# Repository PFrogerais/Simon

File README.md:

# Démonstration du Jeu Simon – Assemblé & Programmé
Dans cette vidéo, découvrez le jeu **Simon** entièrement assemblé et programmé !  

Ce projet, basé sur une carte Arduino, intègre :
- **4 LEDs** et **4 boutons** pour reproduire la séquence du jeu,
- Un **buzzer** pour les signaux sonores,
- Un **boîtier imprimé en 3D** réalisé sur mesure,

# Dossier de conception du shield Arduino

Voici un guide étape par étape pour concevoir et assembler la carte électronique intégrant des composants CMS (résistances et LED montées en surface) ainsi que des composants traversants (comme le connecteur Arduino et le buzzer). Ce procédé  inclut l'application manuelle de pâte à braser et le passage en four à refusion sans utilisation de stencil.

## 1. Génération des Fichiers de Fabrication

- **Fichiers Gerber :**
- Télécharger [fichiers de fabrication gerber Simon3.zip](hardware/kicad/simon3/production/simon3.zip)
- **Fabrication du PCB :**
- Envoyez ces fichiers à un fabricant de PCB (JLCPCB)

## 2. Nomenclature

| Reference         | Value        |  Qty |
|-------------------|--------------|----- |
| BZ1               | Buzzer       |  1   |
| D1                | LED RED      |  1   |
| D2                | LED Green    |  1   |
| D3                | LED Blue     |  1   |
| D4                | LED Yellow   |  1   |
| J1                | Power        |  1   |
| J2,J4             | Digital/PWM  |  2   |
| J3                | Analog       |  1   |
| R1,R2             | 160          |  2   |
| R3                | 100          |  1   |
| R4                | 150          |  1   |
| R5,R6,R7,R8       | 10k          |  4   |
| SW1,SW2,SW3,SW4   | SW_Push      |  4   |

[Nomenclature](hardware/kicad/simon3/simon3.csv)

## 4. Préparation à l’Assemblage

- **Nettoyage du PCB :**
  - Assurez-vous que la carte est propre et exempte de poussière ou d’empreintes.
- **Mise en place du poste de travail :**
  - Organisez votre matériel : pâte à braser (en seringue), fer à souder pour les composants traversants, four à refusion.
- **Documentation :**
  - Imprimez le schéma et/ou un plan de positionnement (layout) pour guider le placement des composants.

# Brasage des composants

## 1. Application de la Pâte à Braser (Sans Stencil)

- **Utilisation d’une seringue :**
  - À l’aide d’une seringue, déposez manuellement la pâte à braser sur chaque zone de montage des composants CMS.
  - Veillez à appliquer la quantité appropriée pour chaque pad afin d’éviter les ponts de soudure ou les soudures insuffisantes.
- **Précision :**
  - Pour les zones très fines, utilisez une seringue à embout fin et, si besoin, une loupe pour vérifier l’exactitude de l’application.

## 6. Placement des Composants CMS

- **Positionnement :**
  - Placez délicatement les composants CMS (résistances, LED, etc.) sur les pads recouverts de pâte.
  - Vérifiez l’alignement et l’orientation (notamment pour les composants polarisés comme certaines LED).
- **Ajustement :**
  - Corrigez la position des composants si nécessaire avant le passage en four.

## 7. Passage en Four à Refusion

- **Programmation de la courbe de chauffe :**

  - Programmez le four à refusion selon une courbe de température adaptée (phase de préchauffage, pic de température, et refroidissement contrôlé).

- **Refusion :**
  - Placez la carte dans le four et lancez le cycle.
  - Surveillez le processus pour vous assurer que la pâte à braser fond correctement et forme des joints solides.
- **Refroidissement :**
  - Laissez la carte refroidir progressivement pour éviter les contraintes thermiques.

## 8. Soudure des Composants Traversants

- **Placement manuel :**
  - Après la refusion des composants CMS, positionnez les composants traversants (connecteur Arduino, buzzer, etc.) sur la carte.
- **Soudure :**
  - Utilisez un fer à souder pour souder manuellement ces composants.
  - Assurez-vous de réaliser des soudures nettes et sans ponts.
- Utilisation d'une carte Arduino HS pour pour maintenir le shield et les connecteurs 

- Placer la carte par dessus 

## 9. Inspection et Tests

- **Contrôle visuel :**

  - Inspectez la carte à l’aide d’une loupe ou d’un microscope pour vérifier la qualité des soudures (absence de ponts, bonne homogénéité des joints).
- **Retouches éventuelles :**
  - Réalisez des retouches manuelles si vous constatez des défauts.
- **Tests fonctionnels :**
  - Alimentez la carte et vérifiez le bon fonctionnement de l’ensemble du circuit (LED, buzzer, connecteur Arduino).
  - Mesurez les tensions et vérifiez la continuité des pistes si nécessaire.

# Conception du boitier en 3D

Cette section décrit les étapes d'assemblage de votre projet dans un boîtier imprimé en 3D. Le but est de fournir toutes les informations nécessaires pour intégrer les composants électroniques (Arduino UNO, shield, etc.) dans le boîtier final. Le modèle 3D du boîtier, au format STL, est mis à disposition pour que vous puissiez le préparer dans votre logiciel de découpe (slicer) et lancer l'impression 3D.

## Détail des étapes

1. **Modèle 3D du boîtier**

   - **Description :**  
     Vous disposez du fichier STL du boîtier, nommé ici "Boitier Simon". Ce fichier est utilisé avec un slicer pour préparer l'impression 3D de la pièce.
   - **Lien :**  
     [Boitier Simon](hardware/Boitier/simon_box_2-MainBox.stl)  
     En cliquant sur ce lien, vous accédez directement au fichier STL hébergé dans le répertoire `hardware/Boitier/` de votre dépôt GitHub.

2. **Ajouter les inserts à chaud à l'aide d'un fer à souder**

   - **Description :**  

     Avant de monter les composants, il est recommandé d'ajouter des inserts (des éléments métalliques ou en plastique spécialement conçus pour recevoir des vis) dans le boîtier.  
     Pour cela, on utilise un fer à souder qui, en chauffant les inserts, permet de les fixer solidement dans la matière imprimée.
   - **Illustration :**  

     Cette image montre le boîtier dans lequel les inserts ont été placés, prêts à recevoir les fixations.

3. **Ajouter la carte Arduino UNO**
   - **Description :**  

     Une fois les inserts en place, la carte Arduino UNO est insérée dans le boîtier.  
     Cette étape assure que l'électronique de base du projet est correctement positionnée et prête à être connectée aux autres composants.

    - **Illustration :**  

     L'image illustre la carte Arduino UNO insérée dans le boîtier, avec les inserts déjà en place.

4. **Ajouter le shield**

   - **Description :**  

     Le shield, qui est une extension pour l'Arduino, est ensuite ajouté sur la carte.  
     Cette étape complète l'intégration de l'électronique, permettant d'ajouter des fonctionnalités supplémentaires (par exemple, gestion d'entrées/sorties, alimentation, etc.).
   - **Illustration :**  
     
     L'image montre le boîtier avec la carte Arduino UNO et le shield monté, indiquant l'évolution de l'assemblage.

5. **Visser les 4 vis dans les inserts**

   - **Description :**  
     Pour finaliser l'assemblage, 4 vis sont insérées dans les inserts prévus à cet effet.  
     Ces vis servent à fixer solidement l'ensemble des composants dans le boîtier, garantissant une bonne stabilité mécanique.
   - **Illustration :**  
       
     Cette dernière image montre l'assemblage complet, où l'ensemble des composants (boîtier, inserts, Arduino, shield) est maintenu par les vis.

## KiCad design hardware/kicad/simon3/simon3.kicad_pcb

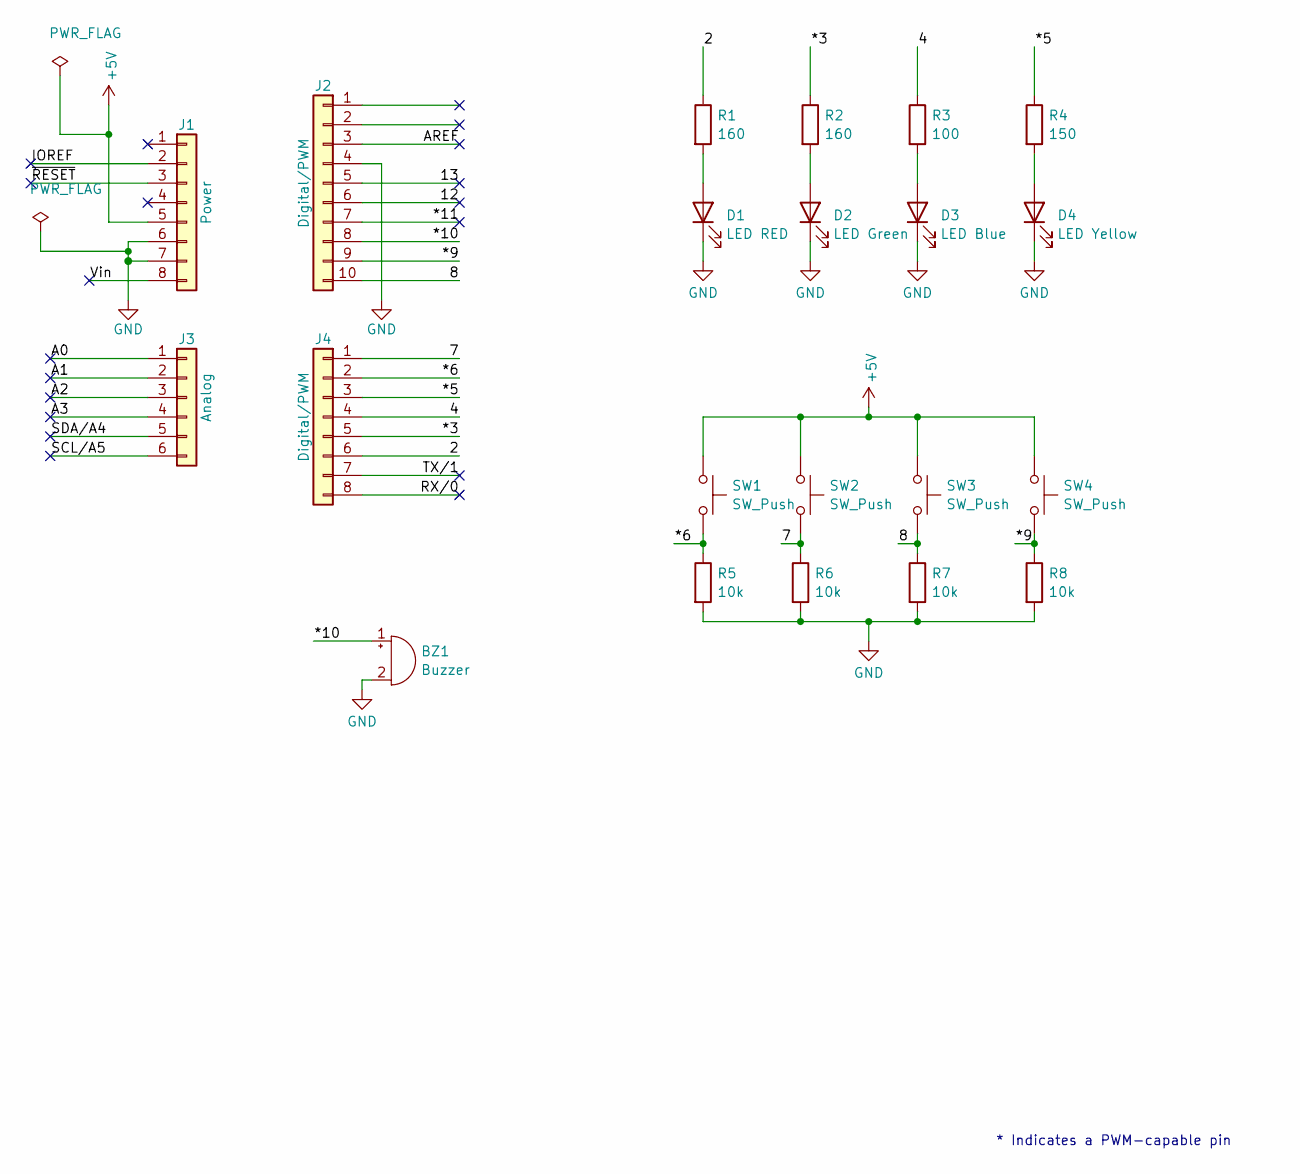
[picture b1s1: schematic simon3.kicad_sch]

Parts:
BZ1: Buzzer; Buzzer_12x9.5RM7.6
D1: LED RED; LED_1206_3216Metric_Pad1.42x1.75mm_HandSolder
D2: LED Green; LED_1206_3216Metric_Pad1.42x1.75mm_HandSolder
D3: LED Blue; LED_1206_3216Metric_Pad1.42x1.75mm_HandSolder
D4: LED Yellow; LED_1206_3216Metric_Pad1.42x1.75mm_HandSolder
J1: Power; PinHeader_1x08_P2.54mm_Vertical
J2: Digital/PWM; PinHeader_1x10_P2.54mm_Vertical
J3: Analog; PinHeader_1x06_P2.54mm_Vertical
J4: Digital/PWM; PinHeader_1x08_P2.54mm_Vertical
R1, R2: 160; R_1206_3216Metric
R3: 100; R_1206_3216Metric
R4: 150; R_1206_3216Metric
R5, R6, R7, R8: 10k; R_1206_3216Metric
SW1, SW2, SW3, SW4: SW_Push; SW_SPST_TL3342

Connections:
+5V: J1.5, SW1.1, SW2.1, SW3.1, SW4.1
/2: J4.6, R1.1
/4: J4.4, R3.1
/7: J4.1, R6.1, SW2.2
/8: J2.10, R7.1, SW3.2
/12: J2.6
/13: J2.5
/*3: J4.5, R2.1
/*5: J4.3, R4.1
/*6: J4.2, R5.1, SW1.2
/*9: J2.9, R8.1, SW4.2
/*10: BZ1.1 (+), J2.8
/*11: J2.7
/A0: J3.1
/A1: J3.2
/A2: J3.3
/A3: J3.4
/AREF: J2.3
/IOREF: J1.2
/RX/0: J4.8
/SCL/A5: J3.6
/SDA/A4: J3.5
/TX/1: J4.7
/Vin: J1.8
/~RESET: J1.3
GND: BZ1.2 (-), D1.1 (K), D2.1 (K), D3.1 (K), D4.1 (K), J1.6, J1.7, J2.4, R5.2, R6.2, R7.2, R8.2
unnamed: D1.2 (A), R1.2
unnamed: D2.2 (A), R2.2
unnamed: D3.2 (A), R3.2
unnamed: D4.2 (A), R4.2

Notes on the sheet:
* Indicates a PWM-capable pin

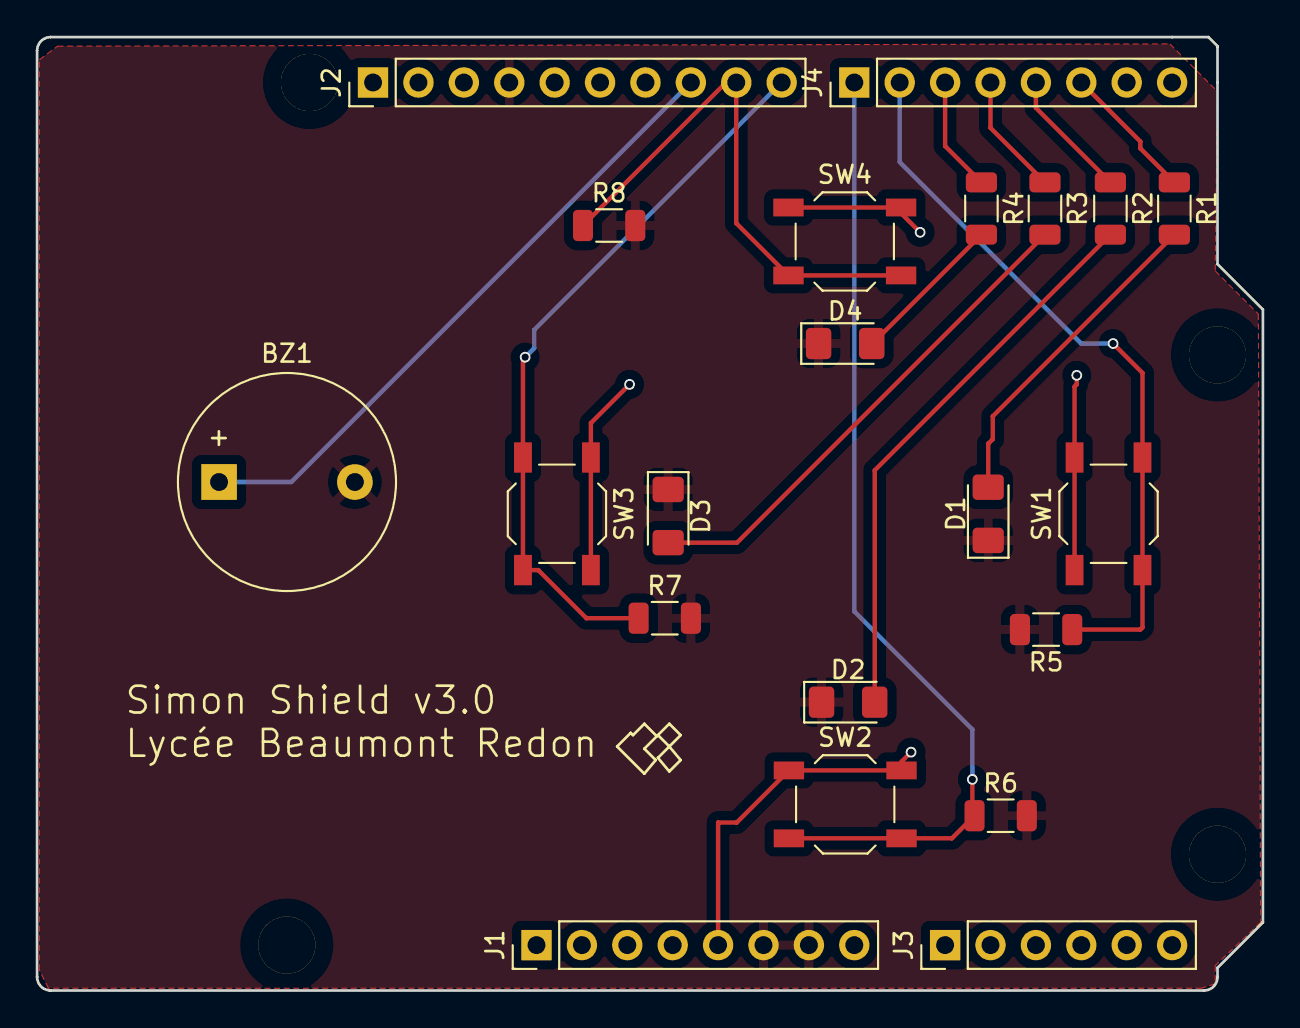
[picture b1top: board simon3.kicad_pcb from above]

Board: 2 copper layers, 68.6 x 53.3 mm, 25 parts (0 on the bottom side), 15 nets.

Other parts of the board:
MH1, MH2, MH3, MH4: MountingHole_3.2mm

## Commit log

2025-02-03 Ajout des projet FreeCAD et kicad du boitier
2025-02-03 Ajout partie Arduino
2025-02-03 Ajout README pour arduino
2025-02-03 ajout image struct
2025-02-03 modeif chemin dans README
2025-02-03 Ajout clours simon.svg
2025-02-03 modif mineurs
2025-02-03 Ajout noueau model shield simon 3
2025-02-04 ajout nomenclature
2025-02-04 sdfsdf
2025-02-04 ajout images
2025-02-04 modif insertion des image
2025-02-04 image9
2025-02-04 images boitier stl
2025-02-04 Ajouer decriptin mise en boiter
2025-02-04 corrction mise en boitier
2025-02-04 modif mise en boitier avec aide IA
2025-02-04 correcions mineurs
2025-02-07 Test
2025-02-07 corrections mineurs
2025-02-07 mise en forme README
2025-02-09 Ajout assemblage modif Readme
2025-02-09 sdfsdfh
2025-02-09 del backup fil
2025-02-09 ajout video
2025-02-09 correction lien
2025-02-09 ajout video thumbnail
2025-02-12 rev minneurs
2025-03-07 modif mineurs README
